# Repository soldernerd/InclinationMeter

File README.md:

# Inclination Meter

A battery-powered, Bluetooth-enabled precision electronic level instrument for machine tool geometry inspection and granite surface plate qualification.

## Overview

The instrument combines a MEMS 3-axis inclinometer (Murata SCL3300) with a high-resolution pendulum-based capacitive sensor (Sciosense PCAP04), a 2.7" Sharp Memory LCD display, and a Bluetooth Low Energy interface to a companion Windows application. All precision sensing is mechanically coupled directly to a cast iron reference base, isolated from the plastic enclosure.

## Hardware

| Parameter | Value |
|---|---|
| MCU | STM32G0B1RET6 (Cortex-M0+, 64 MHz, 512 KB flash) |
| Display | Sharp LS027B7DH01, 2.7", 400x240 monochrome |
| Connectivity | Bluetooth LE 5.0 (Microchip RN4871) |
| USB | USB-C Full Speed - charging + HID + DFU bootloader |
| Battery | 1S LiPo 1000 mAh, ~20 h runtime |
| Supply | 3.3 V main rail, 5 V display rail |
| MEMS range | +/-90 deg |
| Pendulum range | +/-1 mm/m |
| Pendulum resolution | ~0.001 um/m |

### Physical Architecture

Three PCBs:
- **Main board** - MCU, power management, display, BLE, user interface
- **SCL3300 daughter board** - 3-axis MEMS inclinometer, mounted to cast iron base
- **PCAP04 daughter boards x2** - capacitive pendulum readout, one per axis

## Repository Structure

```
KiCad/          KiCad 10 schematic and PCB files
docs/           KiCad file format and schematic reference notes
spec.md         Full hardware design specification
Netlist.md      Schematic netlist / connection list
```

## KiCad Library

All symbols and footprints use [sldrnrd_kicad_lib](https://github.com/soldernerd/sldrnrd_kicad_lib). Clone it as a sibling of this repository:

```
EmbeddedSystems/
├── InclinationMeter/   ← this repo
└── sldrnrd_kicad_lib/  ← library repo
```

## Firmware

Developed with STM32CubeIDE. Firmware update via USB DFU bootloader (no external programmer required after initial flash).

## Status

Hardware design in progress - schematic phase.

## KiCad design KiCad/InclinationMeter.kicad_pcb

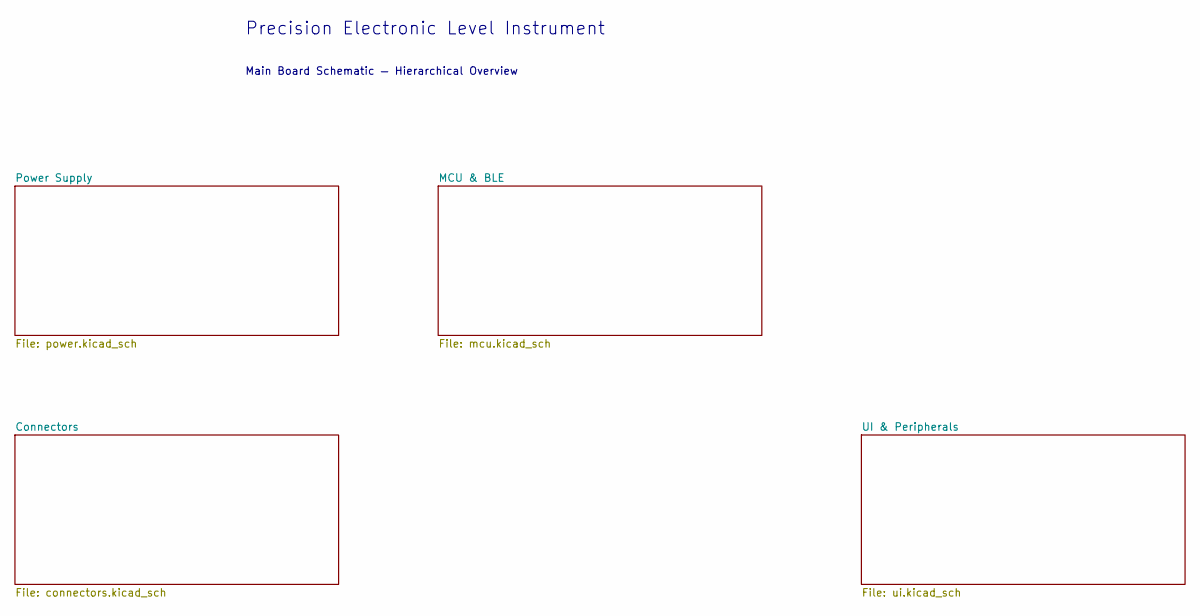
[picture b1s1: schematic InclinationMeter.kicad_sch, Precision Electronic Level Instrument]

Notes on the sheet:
Main Board Schematic — Hierarchical Overview
Precision Electronic Level Instrument

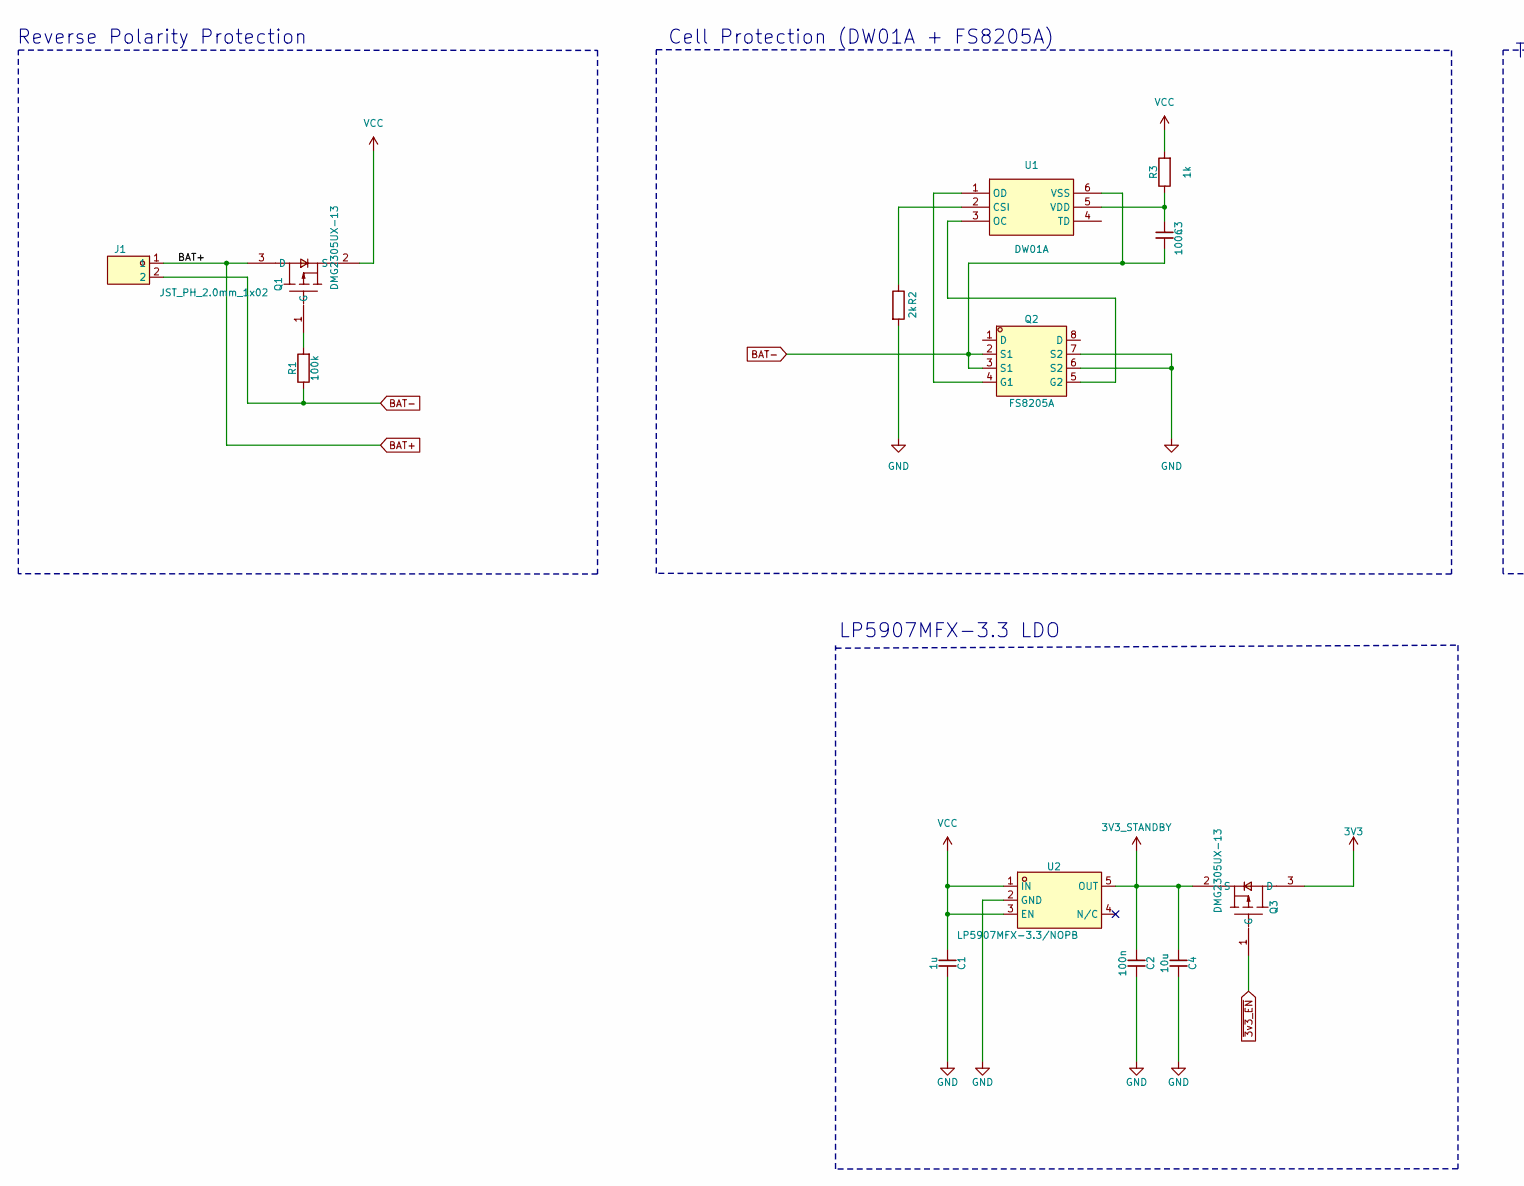
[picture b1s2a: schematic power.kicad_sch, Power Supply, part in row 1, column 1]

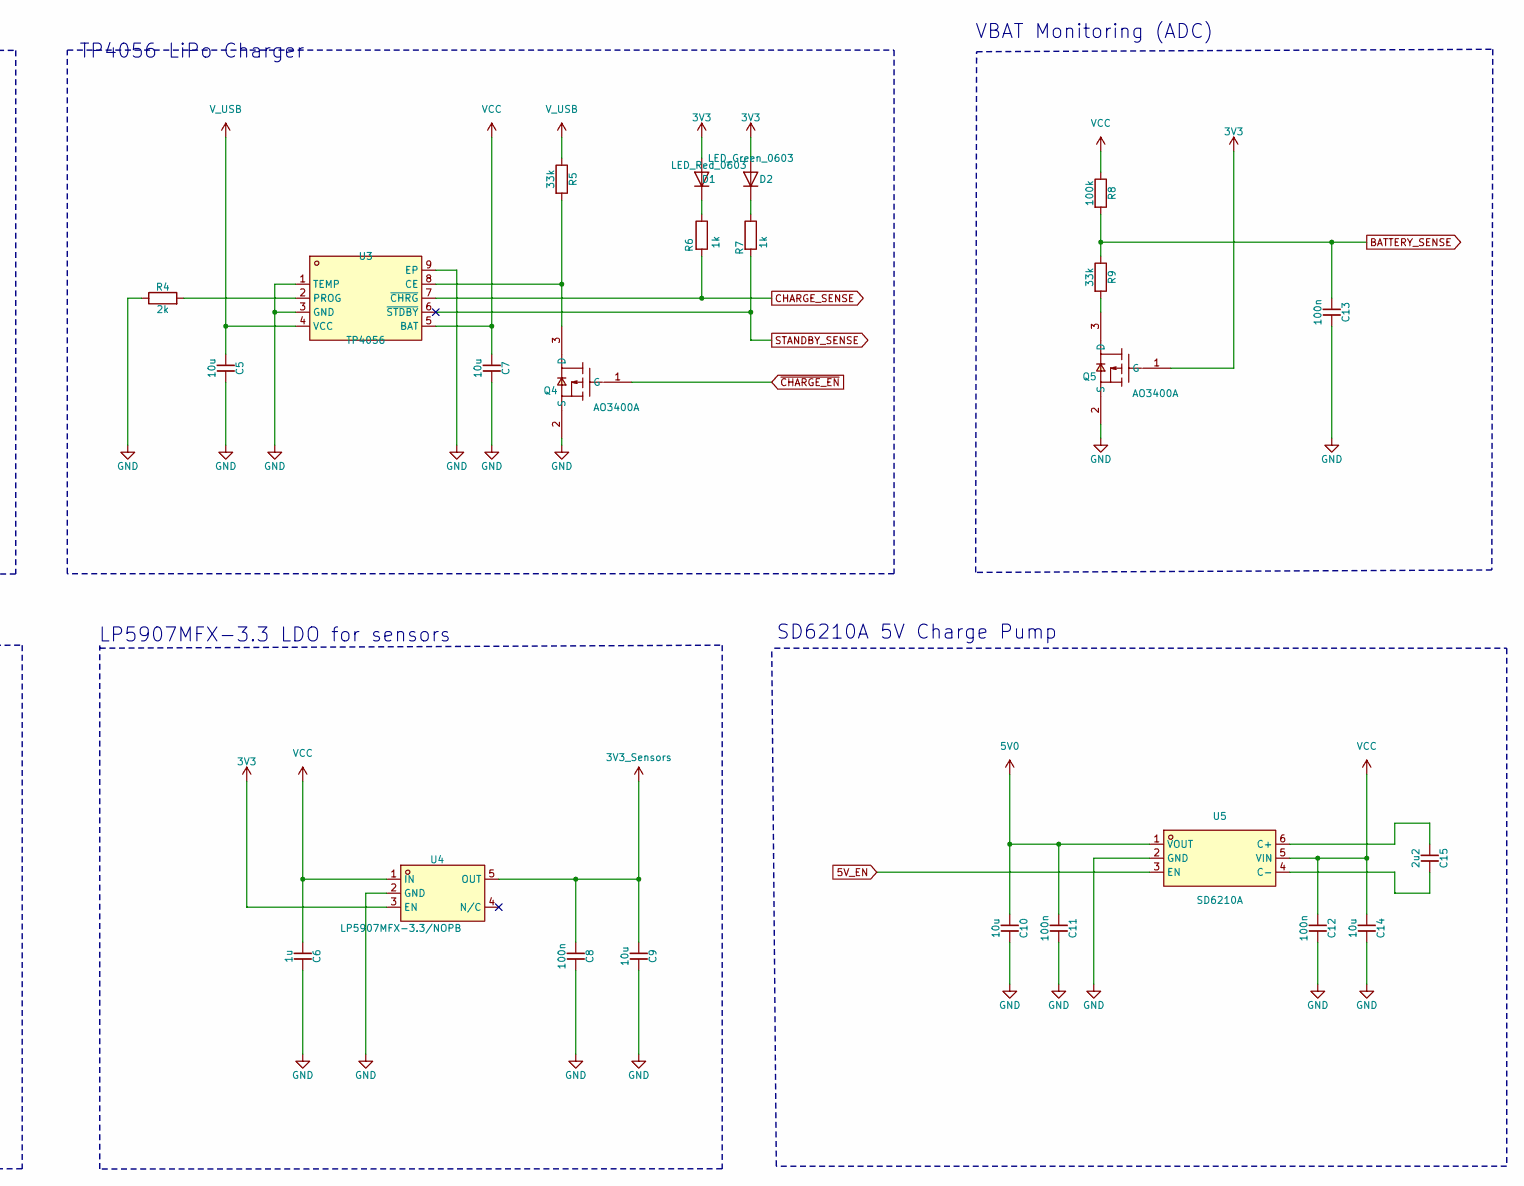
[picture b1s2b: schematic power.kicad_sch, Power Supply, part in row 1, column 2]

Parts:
C1, C6: 1u; C_0805; Voltage 50V; MPN CL21B105KBFNNNE; LCSC C28323
C2, C3, C8, C11, C12, C13: 100n; C_0603; Voltage 50V; MPN CC0603KRX7R9BB104; LCSC C14663
C4, C5, C7, C9, C10, C14: 10u; C_1206; Voltage 25V; MPN CC1206KKX7R8BB106; LCSC C70462
C15: 2u2; C_0805; Voltage 16V; MPN GCM21BR71C225KA64L; LCSC C126589
D1: LED_Red_0603; LED_0603; MPN KT-0603R; LCSC C2286
D2: LED_Green_0603; LED_0603; MPN 19-217/GHC-YR1S2/3T; LCSC C72043
J1: JST_PH_2.0mm_1x02; MPN B2B-PH-K-S; LCSC C131337
Q1, Q3: DMG2305UX-13; SOT-23-3; MPN DMG2305UX-13; LCSC C144153
Q2: FS8205A; TSSOP-8; MPN FS8205A; LCSC C14212
Q4, Q5: AO3400A; SOT-23-3; MPN AO3400A; LCSC C20917
R1, R8: 100k; R_0603; MPN 0603WAF1003T5E; LCSC C25803
R2, R4: 2k; R_0603; MPN 0603WAF2001T5E; LCSC C22975
R3, R6, R7: 1k; R_0603; MPN 0603WAF1001T5E; LCSC C21190
R5, R9: 33k; R_0603; MPN 0603WAF3302T5E; LCSC C4216
U1: DW01A; SOT-23-6; MPN DW01A; LCSC C85680
U2, U4: LP5907MFX-3.3/NOPB; SOT-23-5; MPN LP5907MFX-3.3/NOPB; LCSC C80670
U3: TP4056; ESOP-8; MPN TP4056; LCSC C382139
U5: SD6210A; SOT-23-6; MPN SD6210A; LCSC C250809

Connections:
3V3: D1.1 (A), D2.1 (A), Q3.3 (D), Q5.1 (G), U4.3 (EN); also elsewhere on the board
3V3_STANDBY: C2.1, C4.1, Q3.2 (S), U2.5 (OUT); also elsewhere on the board
3V3_Sensors: C8.1, C9.1, U4.5 (OUT); also elsewhere on the board
5V0: C10.1, C11.1, U5.1 (VOUT); also elsewhere on the board
5V_EN: U5.3 (EN); also elsewhere on the board
~3v3_EN: Q3.1 (G); also elsewhere on the board
BAT+: J1.1, Q1.3 (D)
BAT-: C3.2, J1.2, Q2.2 (S1), Q2.3 (S1), R1.1, U1.6 (VSS)
BATTERY_SENSE: C13.1, R8.2, R9.1; also elsewhere on the board
CHARGE_SENSE: R6.2, U3.7 (~CHRG); also elsewhere on the board
GND: C1.2, C2.2, C4.2, C5.2, C6.2, C7.2, C8.2, C9.2, C10.2, C11.2, C12.2, C13.2, C14.2, Q2.6 (S2), Q2.7 (S2), Q4.2 (S), Q5.2 (S), R2.2, R4.1, U2.2 (GND), U3.1 (TEMP), U3.3 (GND), U3.9 (EP), U4.2 (GND), U5.2 (GND); also elsewhere on the board
unnamed: D1.2 (K), R6.1
unnamed: D2.2 (K), R7.1
unnamed: Q1.1 (G), R1.2
unnamed: Q2.4 (G1), U1.1 (OD)
unnamed: Q2.5 (G2), U1.3 (OC)
unnamed: Q4.3 (D), R5.2, U3.8 (CE)
unnamed: Q5.3 (D), R9.2
unnamed: R2.1, U1.2 (CSI)
unnamed: C3.1, R3.1, U1.5 (VDD)
unnamed: R4.2, U3.2 (PROG)
unnamed: C15.1, U5.6 (C+)
unnamed: C15.2, U5.4 (C-)
STANDBY_SENSE: R7.2, U3.6 (~STDBY); also elsewhere on the board
VCC: C1.1, C6.1, C7.1, C12.1, C14.1, Q1.2 (S), R3.2, R8.1, U2.1 (IN), U2.3 (EN), U3.5 (BAT), U4.1 (IN), U5.5 (VIN)
V_USB: C5.1, R5.1, U3.4 (VCC); also elsewhere on the board
~CHARGE_EN: Q4.1 (G); also elsewhere on the board

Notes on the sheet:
LP5907MFX-3.3 LDO
VBAT Monitoring (ADC)
Cell Protection (DW01A + FS8205A)
TP4056 LiPo Charger
Reverse Polarity Protection
SD6210A 5V Charge Pump
LP5907MFX-3.3 LDO for sensors

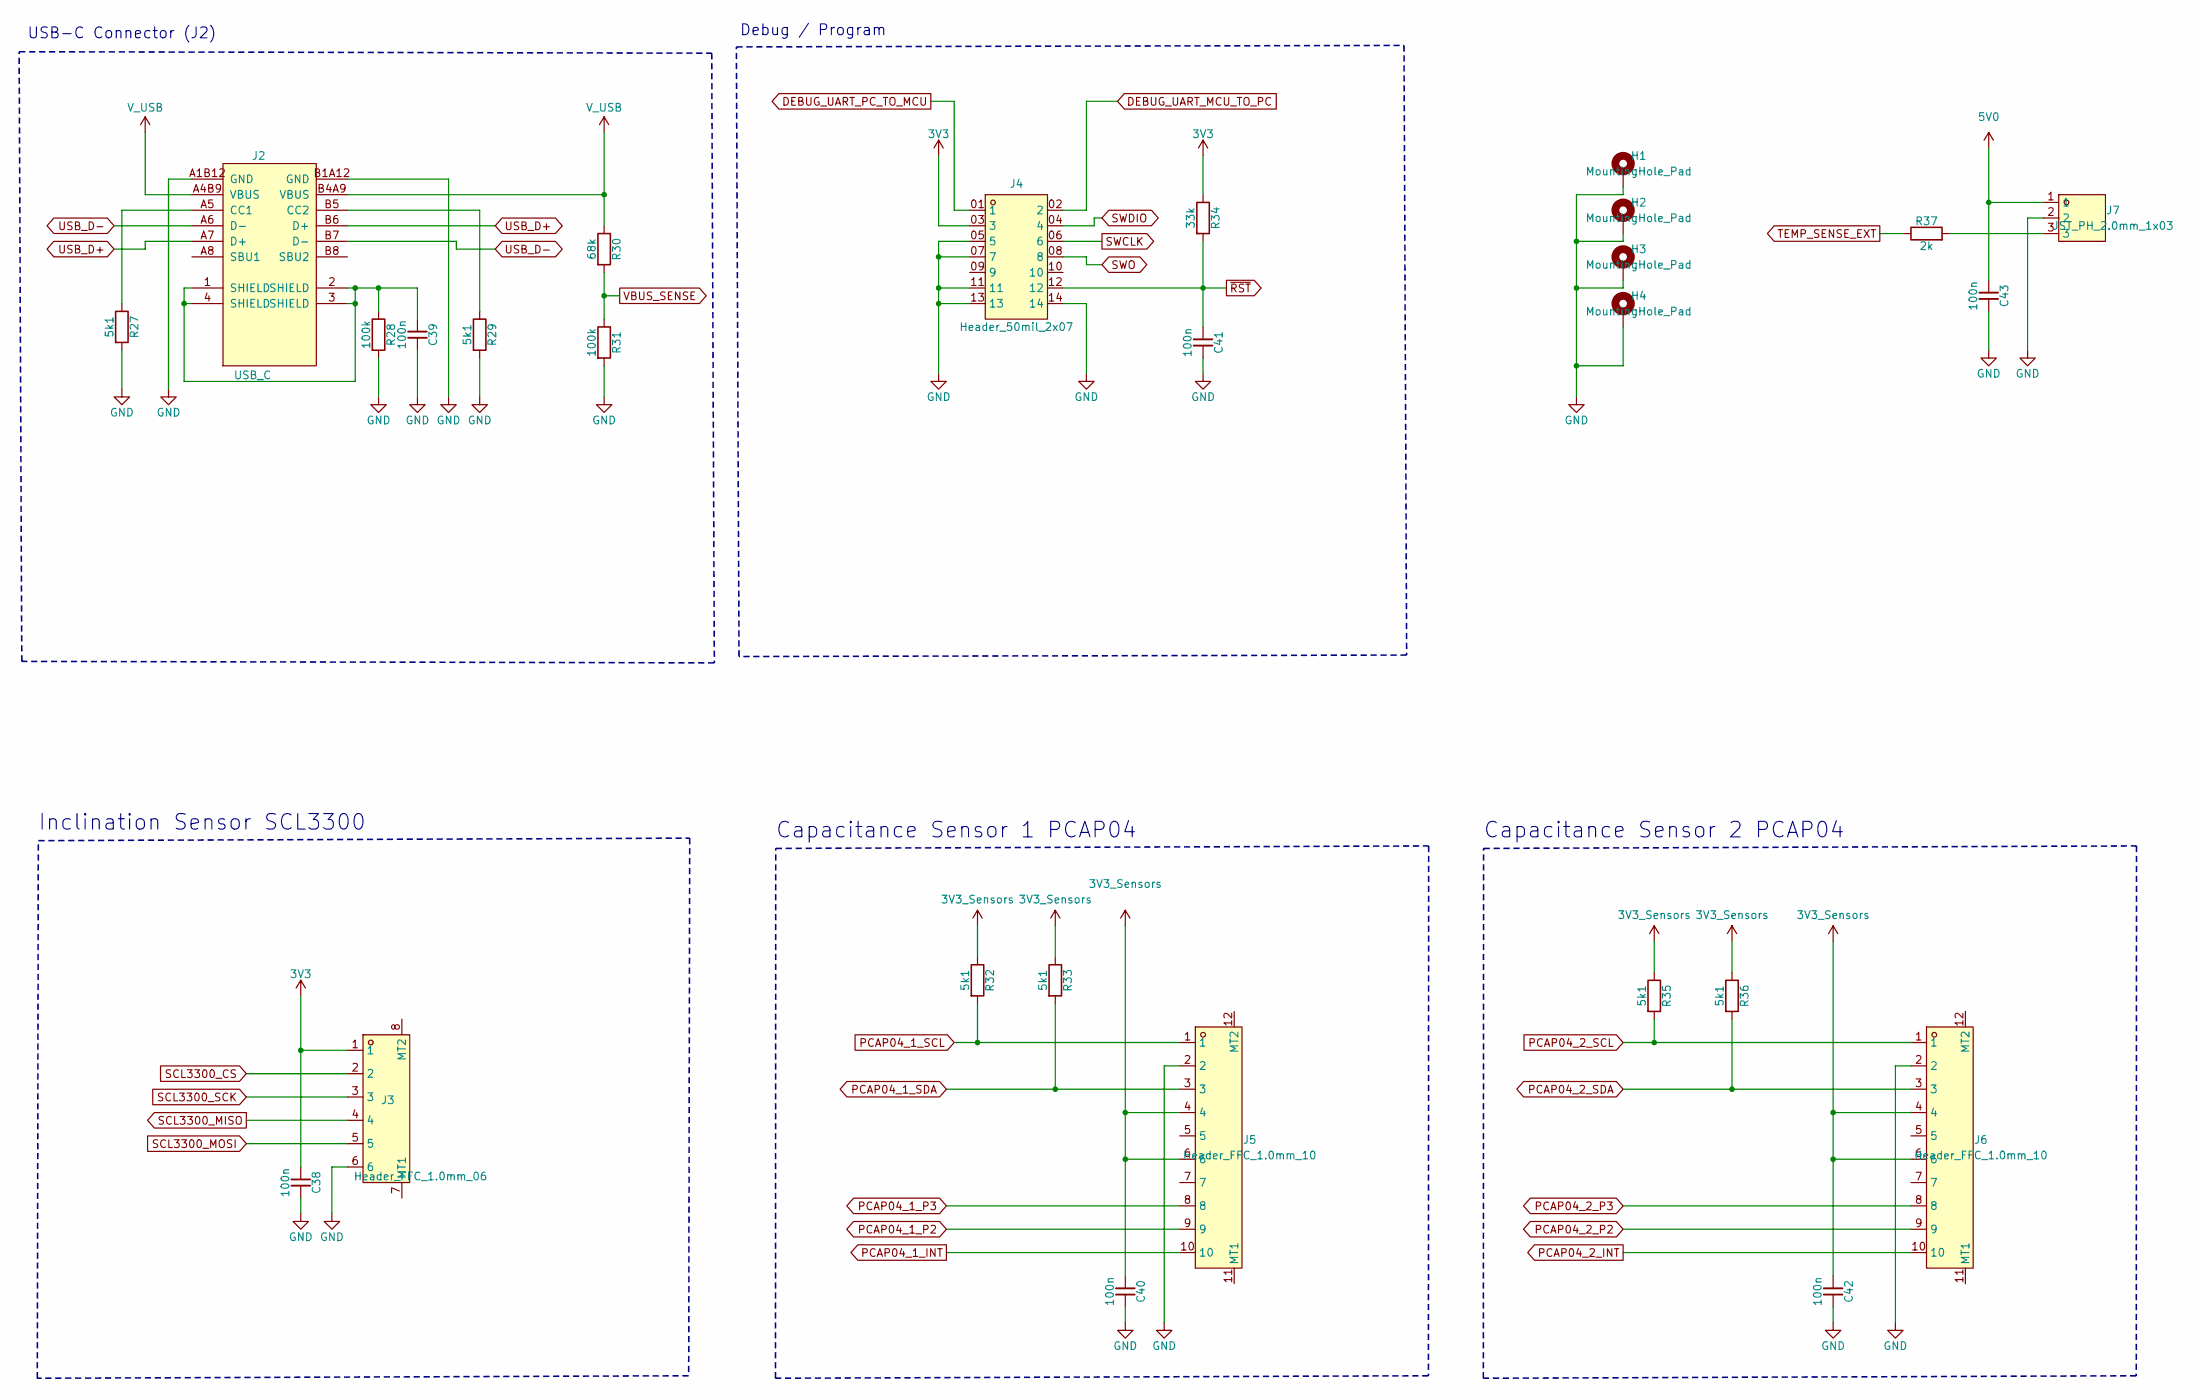
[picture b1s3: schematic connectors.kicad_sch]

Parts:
C38, C39, C40, C41, C42, C43: 100n; C_0603; Voltage 50V; MPN CC0603KRX7R9BB104; LCSC C14663
H1, H2, H3, H4: MountingHole_Pad; MountingHole_3.2mm
J2: USB_C; MPN TYPE-C-31-M-12; LCSC C165948
J3: Header_FFC_1.0mm_06; MPN Header_FFC_1.0mm_06; LCSC C72727
J4: Header_50mil_2x07; LCSC C5563894
J5, J6: Header_FFC_1.0mm_10; MPN Header_FFC_1.0mm_10; LCSC C52162
J7: JST_PH_2.0mm_1x03; MPN B3B-PH-K-S; LCSC C131339
R27, R29, R32, R33, R35, R36: 5k1; R_0603; MPN 0603WAF5101T5E; LCSC C23186
R28, R31: 100k; R_0603; MPN 0603WAF1003T5E; LCSC C25803
R30: 68k; R_0603; MPN 0603WAF6802T5E; LCSC C23231
R34: 33k; R_0603; MPN 0603WAF3302T5E; LCSC C4216
R37: 2k; R_0603; MPN 0603WAF2001T5E; LCSC C22975

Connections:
3V3: C38.1, J3.1, J4.03 (3), R34.1; also elsewhere on the board
3V3_Sensors: C40.1, C42.1, J5.4, J5.6, J6.4, J6.6, R32.1, R33.1, R35.1, R36.1; also elsewhere on the board
5V0: C43.1, J7.1; also elsewhere on the board
DEBUG_UART_MCU_TO_PC: J4.02 (2); also elsewhere on the board
DEBUG_UART_PC_TO_MCU: J4.01 (1); also elsewhere on the board
GND: C38.2, C39.2, C40.2, C41.2, C42.2, C43.2, H1.1 (1_1), H2.1 (1_1), H3.1 (1_1), H4.1 (1_1), J2.A1B12 (GND), J2.B1A12 (GND), J3.6, J4.05 (5), J4.07 (7), J4.11, J4.13, J4.14, J5.2, J6.2, J7.2, R27.2, R28.2, R29.2, R31.2; also elsewhere on the board
unnamed: C39.1, J2.1 (SHIELD), J2.2 (SHIELD), J2.3 (SHIELD), J2.4 (SHIELD), R28.1
unnamed: J2.A5 (CC1), R27.1
unnamed: J2.B5 (CC2), R29.1
unnamed: J7.3, R37.2
PCAP04_1_INT: J5.10; also elsewhere on the board
PCAP04_1_P2: J5.9; also elsewhere on the board
PCAP04_1_P3: J5.8; also elsewhere on the board
PCAP04_1_SCL: J5.1, R32.2; also elsewhere on the board
PCAP04_1_SDA: J5.3, R33.2; also elsewhere on the board
PCAP04_2_INT: J6.10; also elsewhere on the board
PCAP04_2_P2: J6.9; also elsewhere on the board
PCAP04_2_P3: J6.8; also elsewhere on the board
PCAP04_2_SCL: J6.1, R35.2; also elsewhere on the board
PCAP04_2_SDA: J6.3, R36.2; also elsewhere on the board
SCL3300_CS: J3.2; also elsewhere on the board
SCL3300_MISO: J3.4; also elsewhere on the board
SCL3300_MOSI: J3.5; also elsewhere on the board
SCL3300_SCK: J3.3; also elsewhere on the board
SWCLK: J4.06 (6); also elsewhere on the board
SWDIO: J4.04 (4); also elsewhere on the board
SWO: J4.08 (8); also elsewhere on the board
TEMP_SENSE_EXT: R37.1; also elsewhere on the board
USB_D+: J2.A7 (D+), J2.B6 (D+); also elsewhere on the board
USB_D-: J2.A6 (D-), J2.B7 (D-); also elsewhere on the board
VBUS_SENSE: R30.2, R31.1; also elsewhere on the board
V_USB: J2.A4B9 (VBUS), J2.B4A9 (VBUS), R30.1; also elsewhere on the board
~RST: C41.1, J4.12, R34.2; also elsewhere on the board

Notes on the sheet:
Capacitance Sensor 1 PCAP04
USB-C Connector (J2)
Capacitance Sensor 2 PCAP04
Debug / Program
Inclination Sensor SCL3300

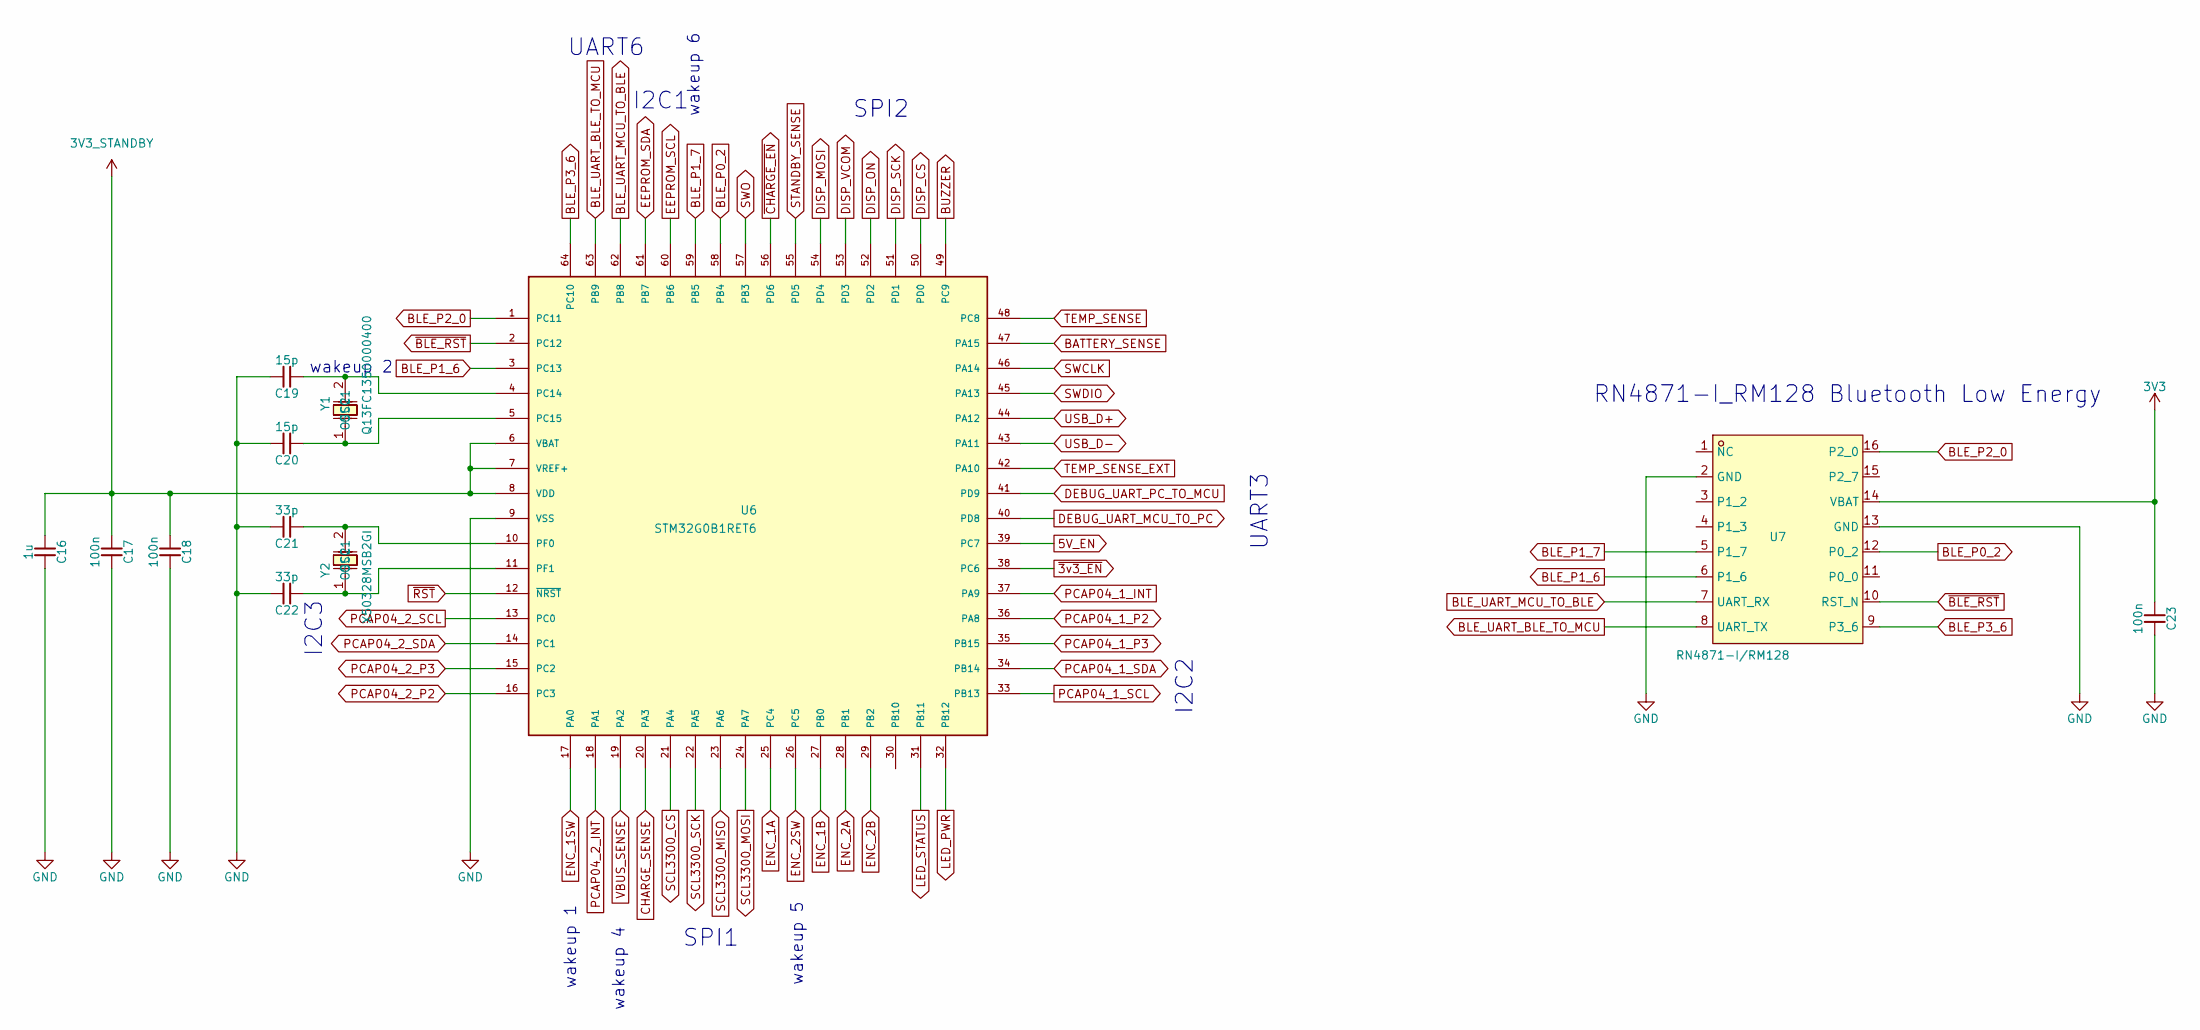
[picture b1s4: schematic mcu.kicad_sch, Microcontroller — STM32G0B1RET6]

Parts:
C16: 1u; C_0805; Voltage 50V; MPN CL21B105KBFNNNE; LCSC C28323
C17, C18, C23: 100n; C_0603; Voltage 50V; MPN CC0603KRX7R9BB104; LCSC C14663
C19, C20: 15p; C_0603; Voltage 50V; MPN CL10C150JB8NNNC; LCSC C1644
C21, C22: 33p; C_0603; Voltage 50V; MPN CL10C330JB8NNNC; LCSC C1663
U6: STM32G0B1RET6; LQFP-64; LCSC C2829307
U7: RN4871-I/RM128; RN4871; MPN RN4871-I/RM128; LCSC C633941
Y1: Q13FC1350000400; CRYSTAL-3215; MPN Q13FC1350000400; LCSC C32346
Y2: X50328MSB2GI; CRYSTAL-3225; MPN X50328MSB2GI; LCSC C115962

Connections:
3V3: C23.1, U7.14 (VBAT); also elsewhere on the board
3V3_STANDBY: C16.1, C17.1, C18.1, U6.6 (VBAT), U6.7 (VREF+), U6.8 (VDD); also elsewhere on the board
5V_EN: U6.39 (PC7); also elsewhere on the board
~3v3_EN: U6.38 (PC6); also elsewhere on the board
BATTERY_SENSE: U6.47 (PA15); also elsewhere on the board
BLE_P0_2: U6.58 (PB4), U7.12 (P0_2)
BLE_P1_6: U6.3 (PC13), U7.6 (P1_6)
BLE_P1_7: U6.59 (PB5), U7.5 (P1_7)
BLE_P2_0: U6.1 (PC11), U7.16 (P2_0)
BLE_P3_6: U6.64 (PC10), U7.9 (P3_6)
BLE_UART_BLE_TO_MCU: U6.63 (PB9), U7.8 (UART_TX)
BLE_UART_MCU_TO_BLE: U6.62 (PB8), U7.7 (UART_RX)
BUZZER: U6.49 (PC9); also elsewhere on the board
CHARGE_SENSE: U6.20 (PA3); also elsewhere on the board
DEBUG_UART_MCU_TO_PC: U6.40 (PD8); also elsewhere on the board
DEBUG_UART_PC_TO_MCU: U6.41 (PD9); also elsewhere on the board
DISP_CS: U6.50 (PD0); also elsewhere on the board
DISP_MOSI: U6.54 (PD4); also elsewhere on the board
DISP_ON: U6.52 (PD2); also elsewhere on the board
DISP_SCK: U6.51 (PD1); also elsewhere on the board
DISP_VCOM: U6.53 (PD3); also elsewhere on the board
EEPROM_SCL: U6.60 (PB6); also elsewhere on the board
EEPROM_SDA: U6.61 (PB7); also elsewhere on the board
ENC_1A: U6.25 (PC4); also elsewhere on the board
ENC_1B: U6.27 (PB0); also elsewhere on the board
ENC_1SW: U6.17 (PA0); also elsewhere on the board
ENC_2A: U6.28 (PB1); also elsewhere on the board
ENC_2B: U6.29 (PB2); also elsewhere on the board
ENC_2SW: U6.26 (PC5); also elsewhere on the board
GND: C16.2, C17.2, C18.2, C19.2, C20.2, C21.2, C22.2, C23.2, U6.9 (VSS), U7.2 (GND), U7.13 (GND); also elsewhere on the board
LED_PWR: U6.32 (PB12); also elsewhere on the board
LED_STATUS: U6.31 (PB11); also elsewhere on the board
unnamed: C19.1, U6.4 (PC14), Y1.2 (OSC2)
unnamed: C20.1, U6.5 (PC15), Y1.1 (OSC1)
unnamed: C21.1, U6.10 (PF0), Y2.2 (OSC2)
unnamed: C22.1, U6.11 (PF1), Y2.1 (OSC1)
PCAP04_1_INT: U6.37 (PA9); also elsewhere on the board
PCAP04_1_P2: U6.36 (PA8); also elsewhere on the board
PCAP04_1_P3: U6.35 (PB15); also elsewhere on the board
PCAP04_1_SCL: U6.33 (PB13); also elsewhere on the board
PCAP04_1_SDA: U6.34 (PB14); also elsewhere on the board
PCAP04_2_INT: U6.18 (PA1); also elsewhere on the board
PCAP04_2_P2: U6.16 (PC3); also elsewhere on the board
PCAP04_2_P3: U6.15 (PC2); also elsewhere on the board
PCAP04_2_SCL: U6.13 (PC0); also elsewhere on the board
PCAP04_2_SDA: U6.14 (PC1); also elsewhere on the board
SCL3300_CS: U6.21 (PA4); also elsewhere on the board
SCL3300_MISO: U6.23 (PA6); also elsewhere on the board
SCL3300_MOSI: U6.24 (PA7); also elsewhere on the board
SCL3300_SCK: U6.22 (PA5); also elsewhere on the board
STANDBY_SENSE: U6.55 (PD5); also elsewhere on the board
SWCLK: U6.46 (PA14); also elsewhere on the board
SWDIO: U6.45 (PA13); also elsewhere on the board
SWO: U6.57 (PB3); also elsewhere on the board
TEMP_SENSE: U6.48 (PC8); also elsewhere on the board
TEMP_SENSE_EXT: U6.42 (PA10); also elsewhere on the board
USB_D+: U6.44 (PA12); also elsewhere on the board
USB_D-: U6.43 (PA11); also elsewhere on the board
VBUS_SENSE: U6.19 (PA2); also elsewhere on the board
~BLE_RST: U6.2 (PC12), U7.10 (RST_N)
~CHARGE_EN: U6.56 (PD6); also elsewhere on the board
~RST: U6.12 (~NRST); also elsewhere on the board

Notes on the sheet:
SPI1
wakeup 2
wakeup 1
I2C2
SPI2
wakeup 5
I2C3
wakeup 4
I2C1
UART6
wakeup 6
RN4871-I_RM128 Bluetooth Low Energy
UART3

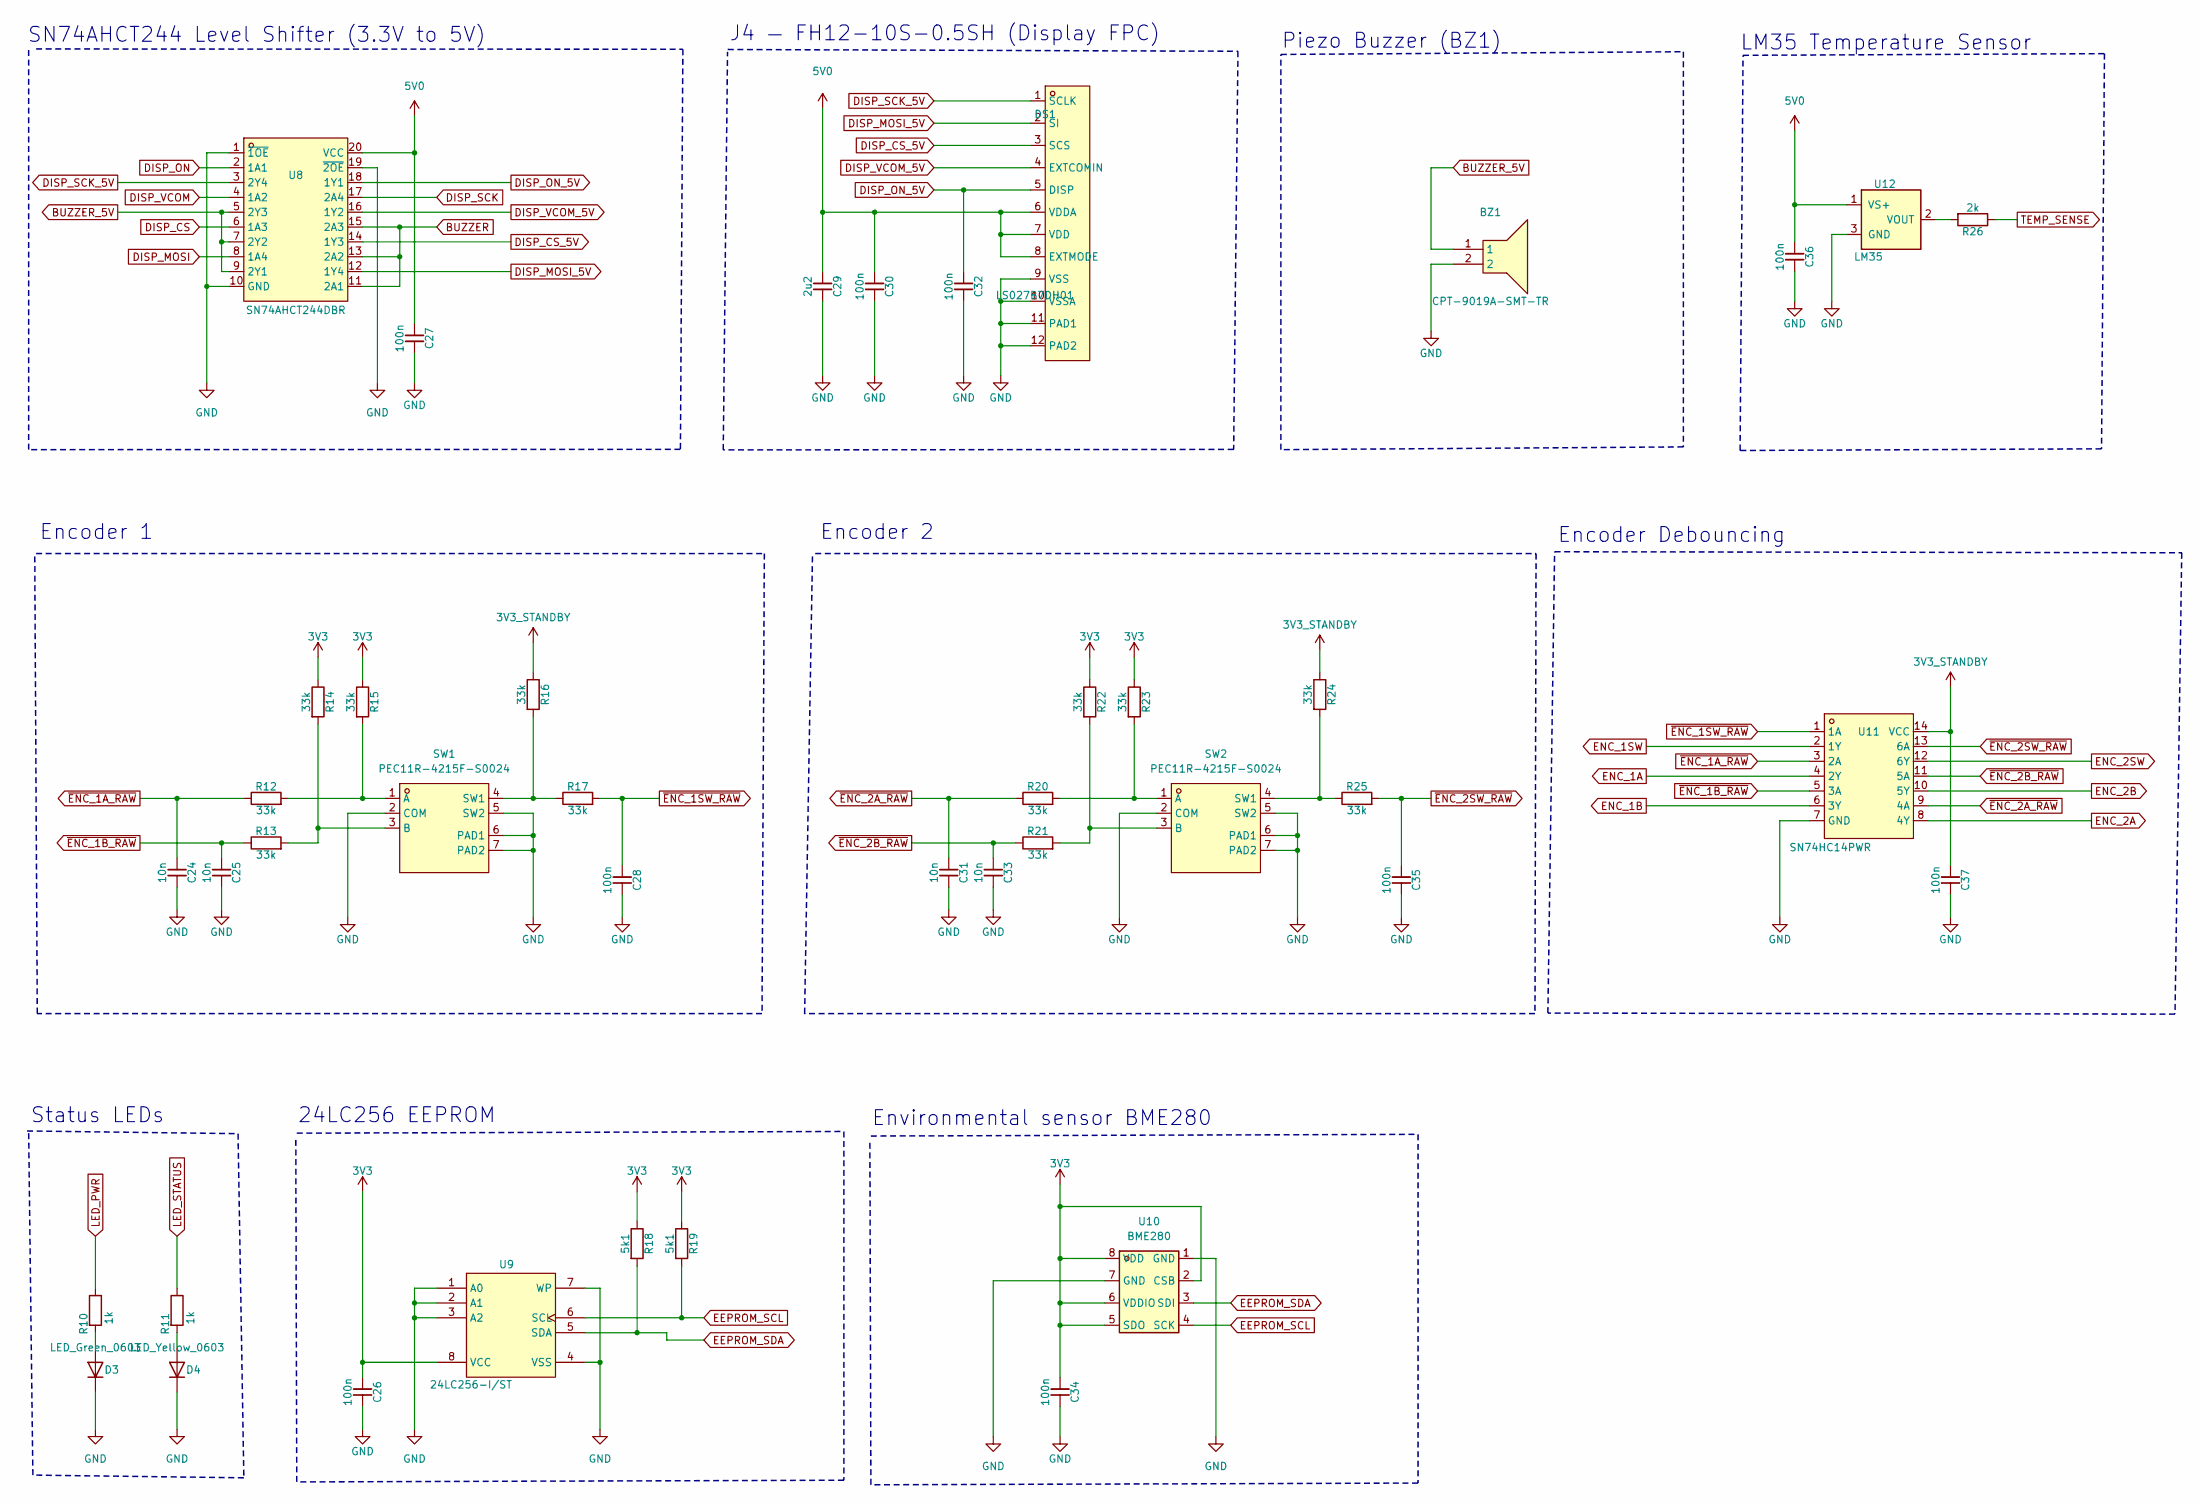
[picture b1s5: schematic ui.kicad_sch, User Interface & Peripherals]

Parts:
BZ1: CPT-9019A-SMT-TR; CPT-9019A; MPN CPT-9019A-SMT-TR; LCSC C20181991
C24, C25, C31, C33: 10n; C_0603; Voltage 50V; MPN 0603B103K500NT; LCSC C57112
C26, C27, C28, C30, C32, C34, C35, C36, C37: 100n; C_0603; Voltage 50V; MPN CC0603KRX7R9BB104; LCSC C14663
C29: 2u2; C_0805; Voltage 16V; MPN GCM21BR71C225KA64L; LCSC C126589
D3: LED_Green_0603; LED_0603; MPN 19-217/GHC-YR1S2/3T; LCSC C72043
D4: LED_Yellow_0603; LED_0603; MPN KT-0603Y; LCSC C2287
DS1: LS027B7DH01; Display_LS027B7DH01; MPN LS027B7DH01; LCSC C17492463
R10, R11: 1k; R_0603; MPN 0603WAF1001T5E; LCSC C21190
R12, R13, R14, R15, R16, R17, R20, R21, R22, R23, R24, R25: 33k; R_0603; MPN 0603WAF3302T5E; LCSC C4216
R18, R19: 5k1; R_0603; MPN 0603WAF5101T5E; LCSC C23186
R26: 2k; R_0603; MPN 0603WAF2001T5E; LCSC C22975
SW1, SW2: PEC11R-4215F-S0024; RotaryEncoder_PEC11R; MPN PEC11R-4215F-S0024; LCSC C143790
U8: SN74AHCT244DBR; SSOP-20; MPN SN74AHCT244DBR; LCSC C2868870
U9: 24LC256-I/ST; TSSOP-8; MPN 24LC256-I/ST; LCSC C87823
U10: BME280; LGA-8_2.5x2.5mm_P0.65mm; MPN BME280; LCSC C92489
U11: SN74HC14PWR; TSSOP-14; MPN SN74HC14PWR; LCSC C6821
U12: LM35; SOT-23-3; LCSC C9900081740

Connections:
3V3: C26.1, C34.1, R14.1, R15.1, R18.1, R19.1, R22.1, R23.1, U9.8 (VCC), U10.2 (CSB), U10.5 (SDO), U10.6 (VDDIO), U10.8 (VDD); also elsewhere on the board
3V3_STANDBY: C37.1, R16.1, R24.1, U11.14 (VCC); also elsewhere on the board
5V0: C27.1, C29.1, C30.1, C36.1, DS1.6 (VDDA), DS1.7 (VDD), DS1.8 (EXTMODE), U8.20 (VCC), U12.1 (VS+); also elsewhere on the board
BUZZER: U8.11 (2A1), U8.13 (2A2), U8.15 (2A3); also elsewhere on the board
BUZZER_5V: BZ1.1, U8.5 (2Y3), U8.7 (2Y2), U8.9 (2Y1)
DISP_CS: U8.6 (1A3); also elsewhere on the board
DISP_CS_5V: DS1.3 (SCS), U8.14 (1Y3)
DISP_MOSI: U8.8 (1A4); also elsewhere on the board
DISP_MOSI_5V: DS1.2 (SI), U8.12 (1Y4)
DISP_ON: U8.2 (1A1); also elsewhere on the board
DISP_ON_5V: C32.1, DS1.5 (DISP), U8.18 (1Y1)
DISP_SCK: U8.17 (2A4); also elsewhere on the board
DISP_SCK_5V: DS1.1 (SCLK), U8.3 (2Y4)
DISP_VCOM: U8.4 (1A2); also elsewhere on the board
DISP_VCOM_5V: DS1.4 (EXTCOMIN), U8.16 (1Y2)
EEPROM_SCL: R19.2, U9.6 (SCL), U10.4 (SCK); also elsewhere on the board
EEPROM_SDA: R18.2, U9.5 (SDA), U10.3 (SDI); also elsewhere on the board
ENC_1A: U11.4 (2Y); also elsewhere on the board
ENC_1B: U11.6 (3Y); also elsewhere on the board
ENC_1SW: U11.2 (1Y); also elsewhere on the board
ENC_2A: U11.8 (4Y); also elsewhere on the board
ENC_2B: U11.10 (5Y); also elsewhere on the board
ENC_2SW: U11.12 (6Y); also elsewhere on the board
GND: BZ1.2, C24.2, C25.2, C26.2, C27.2, C28.2, C29.2, C30.2, C31.2, C32.2, C33.2, C34.2, C35.2, C36.2, C37.2, D3.2 (K), D4.2 (K), DS1.9 (VSS), DS1.10 (VSSA), DS1.11 (PAD1), DS1.12 (PAD2), SW1.2 (COM), SW1.5 (SW2), SW1.6 (PAD1), SW1.7 (PAD2), SW2.2 (COM), SW2.5 (SW2), SW2.6 (PAD1), SW2.7 (PAD2), U8.1 (~1OE), U8.10 (GND), U8.19 (~2OE), U9.1 (A0), U9.2 (A1), U9.3 (A2), U9.4 (VSS), U9.7 (WP), U10.1 (GND), U10.7 (GND), U11.7 (GND), U12.3 (GND); also elsewhere on the board
LED_PWR: R10.1; also elsewhere on the board
LED_STATUS: R11.1; also elsewhere on the board
unnamed: D3.1 (A), R10.2
unnamed: D4.1 (A), R11.2
unnamed: R12.2, R15.2, SW1.1 (A)
unnamed: R13.2, R14.2, SW1.3 (B)
unnamed: R16.2, R17.1, SW1.4 (SW1)
unnamed: R20.2, R23.2, SW2.1 (A)
unnamed: R21.2, R22.2, SW2.3 (B)
unnamed: R24.2, R25.1, SW2.4 (SW1)
unnamed: R26.2, U12.2 (VOUT)
TEMP_SENSE: R26.1; also elsewhere on the board
~ENC_1A_RAW: C24.1, R12.1, U11.3 (2A)
~ENC_1B_RAW: C25.1, R13.1, U11.5 (3A)
~ENC_1SW_RAW: C28.1, R17.2, U11.1 (1A)
~ENC_2A_RAW: C31.1, R20.1, U11.9 (4A)
~ENC_2B_RAW: C33.1, R21.1, U11.11 (5A)
~ENC_2SW_RAW: C35.1, R25.2, U11.13 (6A)

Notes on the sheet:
Encoder 2
Encoder Debouncing
Status LEDs
LM35 Temperature Sensor
SN74AHCT244 Level Shifter (3.3V to 5V)
Environmental sensor BME280
24LC256 EEPROM
J4 — FH12-10S-0.5SH (Display FPC)
Piezo Buzzer (BZ1)
Encoder 1
